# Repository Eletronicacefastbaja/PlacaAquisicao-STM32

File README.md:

# PlacaAquisicao-STM32
Repositório do Projeto da Placa de Aquisição para o micro-controlador STM32

# TODO

- Adicionar AMP-OP nas entradads analógicas
- Diminuir o tamanho da placa

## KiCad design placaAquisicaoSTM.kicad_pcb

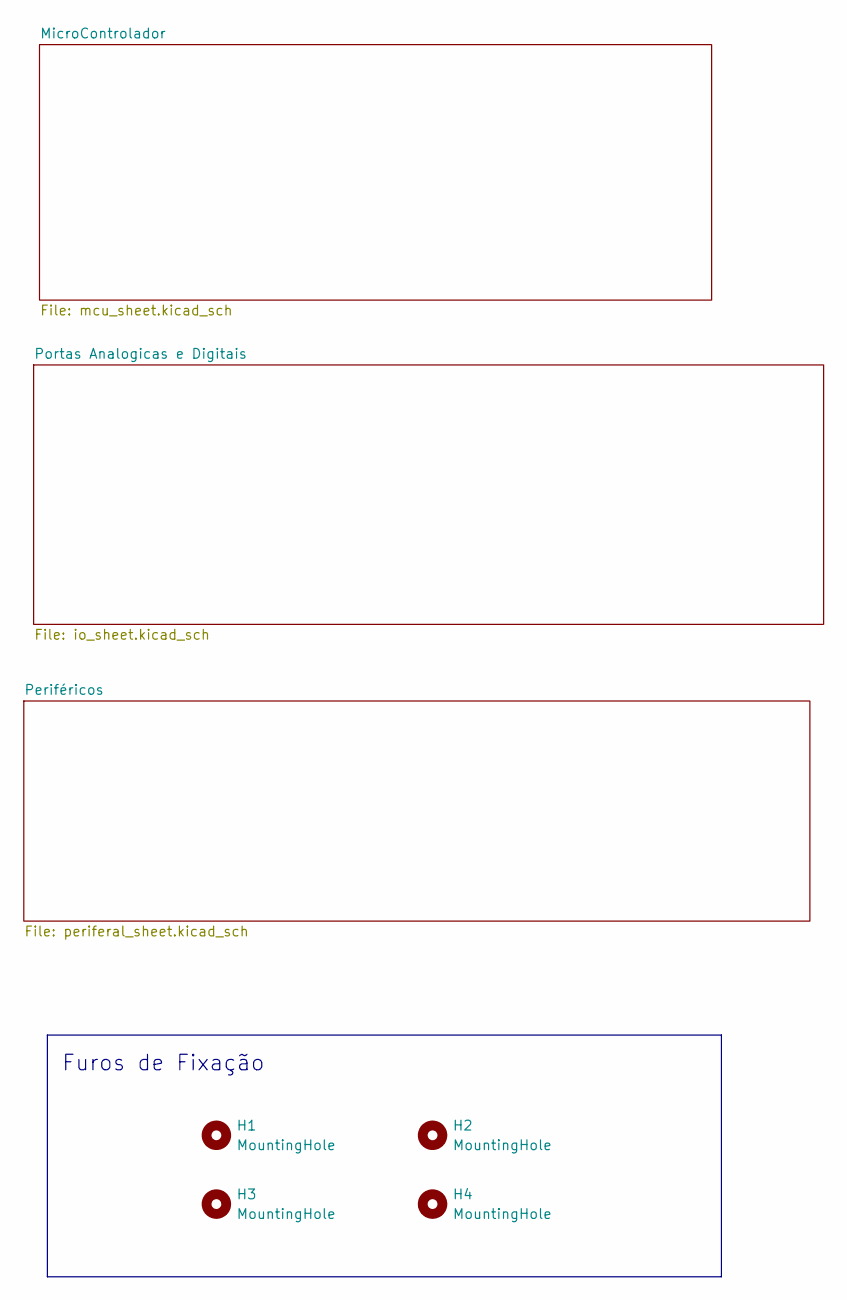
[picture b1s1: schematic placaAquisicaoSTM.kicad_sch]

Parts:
H1, H2, H3, H4: MountingHole; MountingHole_4.3mm_M4_DIN965_Pad

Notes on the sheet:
Furos de Fixação

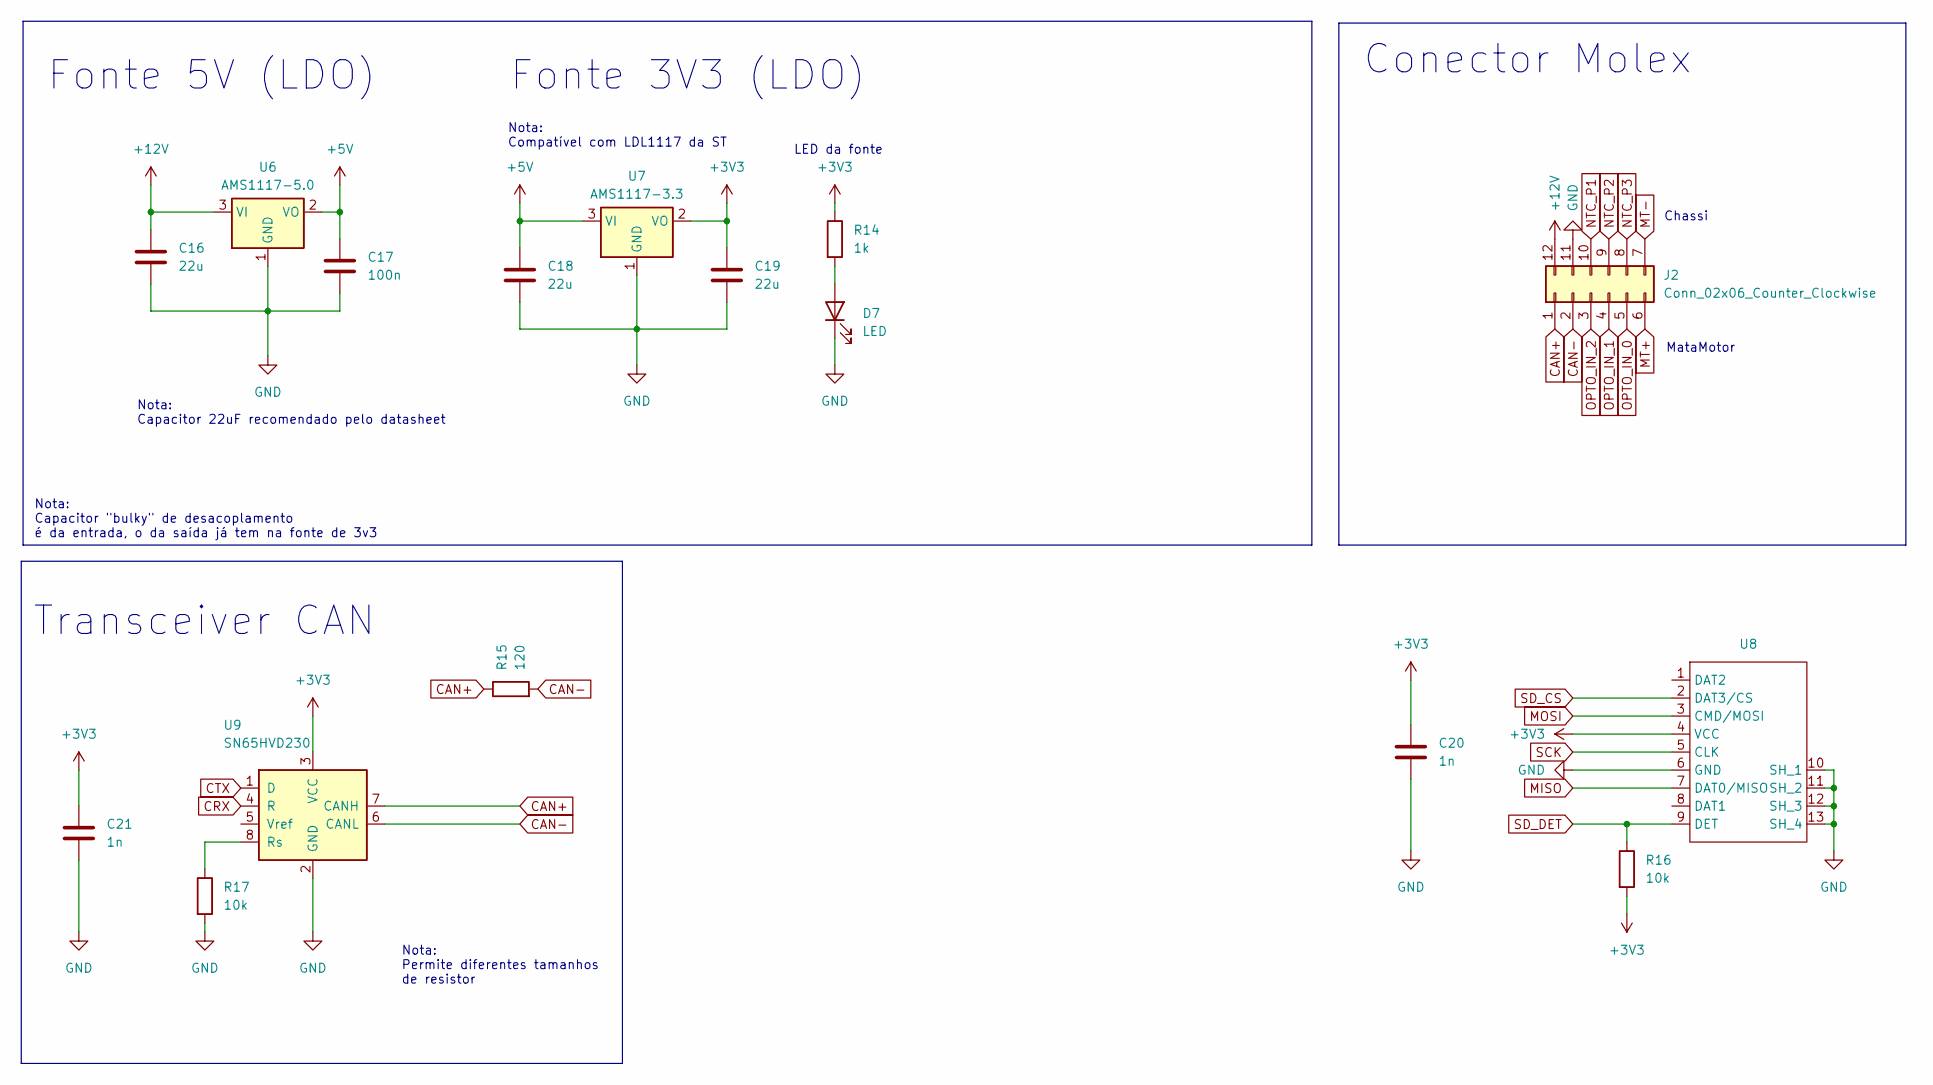
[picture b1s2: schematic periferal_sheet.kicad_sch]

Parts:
C16, C18, C19: 22u; CP_Radial_D6.3mm_P2.50mm
C17: 100n; C_0603_1608Metric_Pad1.08x0.95mm_HandSolder
C20, C21: 1n; C_0603_1608Metric_Pad1.08x0.95mm_HandSolder
D7: LED; LED_1210_HandSoldering
J2: Conn_02x06_Counter_Clockwise; DTM1512PA
R14: 1k; R_1206_3216Metric_Pad1.30x1.75mm_HandSolder
R15: 120; R_0603_1608Metric_Pad0.98x0.95mm_HandSolder
R16, R17: 10k; R_1206_3216Metric_Pad1.30x1.75mm_HandSolder
U6: AMS1117-5.0; SOT-223-3_TabPin2
U7: AMS1117-3.3; SOT-223-3_TabPin2
U8: SD-CARD-GENERIC
U9: SN65HVD230; SOIC-8_3.9x4.9mm_P1.27mm

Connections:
+3V3: C19.1, C20.1, C21.1, R14.1, R16.2, U7.2 (VO), U8.4 (VCC), U9.3 (VCC); also elsewhere on the board
+5V: C17.1, C18.1, U6.2 (VO), U7.3 (VI)
+12V: C16.1, J2.12, U6.3 (VI)
CAN+: J2.1, R15.1, U9.7 (CANH)
CAN-: J2.2, R15.2, U9.6 (CANL)
CRX: U9.4 (R); also elsewhere on the board
CTX: U9.1 (D); also elsewhere on the board
GND: C16.2, C17.2, C18.2, C19.2, C20.2, C21.2, D7.1 (K), J2.11, R17.2, U6.1 (GND), U7.1 (GND), U8.6 (GND), U8.10 (SH_1), U8.11 (SH_2), U8.12 (SH_3), U8.13 (SH_4), U9.2 (GND); also elsewhere on the board
MISO: U8.7 (DAT0/MISO); also elsewhere on the board
MOSI: U8.3 (CMD/MOSI); also elsewhere on the board
MT+: J2.6; also elsewhere on the board
MT-: J2.7; also elsewhere on the board
NTC_P1: J2.10; also elsewhere on the board
NTC_P2: J2.9; also elsewhere on the board
NTC_P3: J2.8; also elsewhere on the board
unnamed: D7.2 (A), R14.2
unnamed: R17.1, U9.8 (Rs)
OPTO_IN_0: J2.5; also elsewhere on the board
OPTO_IN_1: J2.4; also elsewhere on the board
OPTO_IN_2: J2.3; also elsewhere on the board
SCK: U8.5 (CLK); also elsewhere on the board
SD_CS: U8.2 (DAT3/CS); also elsewhere on the board
SD_DET: R16.1, U8.9 (DET); also elsewhere on the board

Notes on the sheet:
Chassi
Fonte 3V3 (LDO)
MataMotor
Fonte 5V (LDO)
Transceiver CAN
Nota: Permite diferentes tamanhos de resistor
LED da fonte
Conector Molex
Nota: Compatível com LDL1117 da ST
Nota: Capacitor 22uF recomendado pelo datasheet
Nota: Capacitor "bulky" de desacoplamento é da entrada, o da saída já tem na fonte de 3v3

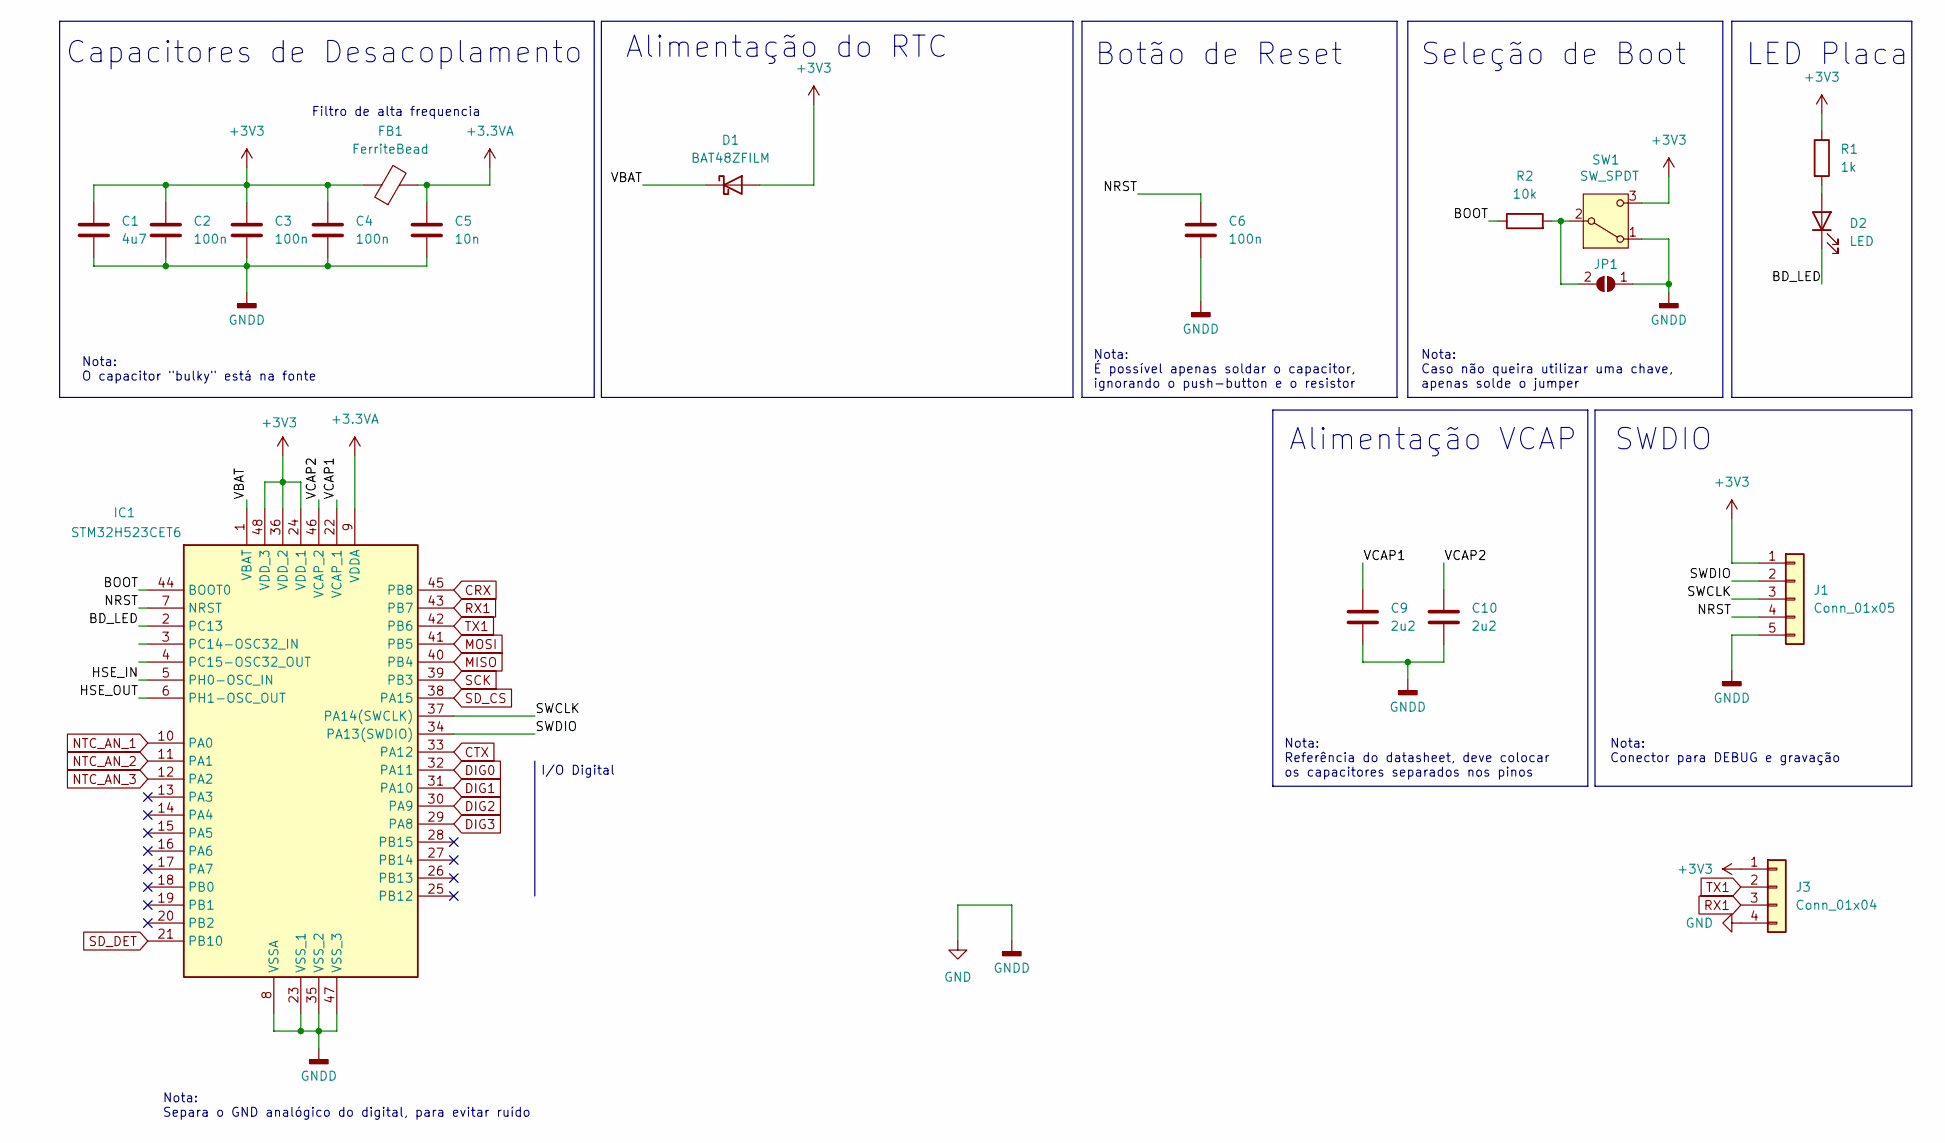
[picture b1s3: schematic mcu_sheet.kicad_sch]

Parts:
C1: 4u7; C_0805_2012Metric_Pad1.18x1.45mm_HandSolder
C2, C3, C4, C6: 100n; C_0603_1608Metric_Pad1.08x0.95mm_HandSolder
C5: 10n; C_0603_1608Metric_Pad1.08x0.95mm_HandSolder
C9, C10: 2u2; C_0603_1608Metric_Pad1.08x0.95mm_HandSolder
D1: BAT48ZFILM; D_SOD-123
D2: LED; LED_1210_HandSoldering
FB1: FerriteBead; L_0805_2012Metric_Pad1.15x1.40mm_HandSolder
IC1: STM32H523CET6; QFP50P900X900X160-48N; Mouser Part Number 511-STM32H523CET6
J1: Conn_01x05; PinHeader_1x05_P2.54mm_Vertical
J3: Conn_01x04; Molex_KK-254_AE-6410-04A_1x04_P2.54mm_Vertical
JP1: SolderJumper_2_Open; SolderJumper-2_P1.3mm_Open_RoundedPad1.0x1.5mm
R1: 1k; R_1206_3216Metric_Pad1.30x1.75mm_HandSolder
R2: 10k; R_1206_3216Metric_Pad1.30x1.75mm_HandSolder
SW1: SW_SPDT; PinHeader_1x03_P2.54mm_Vertical

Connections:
+3.3VA: C5.1, FB1.2, IC1.9 (VDDA)
+3V3: C1.1, C2.1, C3.1, C4.1, D1.2 (A), FB1.1, IC1.24 (VDD_1), IC1.36 (VDD_2), IC1.48 (VDD_3), J1.1, J3.1, R1.1, SW1.3 (C); also elsewhere on the board
/MicroControlador/BD_LED: D2.1 (K), IC1.2 (PC13)
/MicroControlador/BOOT: IC1.44 (BOOT0), R2.1
/MicroControlador/HSE_IN: IC1.5 (PH0-OSC_IN)
/MicroControlador/HSE_OUT: IC1.6 (PH1-OSC_OUT)
/MicroControlador/NRST: C6.1, IC1.7 (NRST), J1.4
/MicroControlador/SWCLK: IC1.37 (PA14(SWCLK)), J1.3
/MicroControlador/SWDIO: IC1.34 (PA13(SWDIO)), J1.2
/MicroControlador/VBAT: D1.1 (K), IC1.1 (VBAT)
/MicroControlador/VCAP1: C9.1, IC1.22 (VCAP_1)
/MicroControlador/VCAP2: C10.1, IC1.46 (VCAP_2)
CRX: IC1.45 (PB8); also elsewhere on the board
CTX: IC1.33 (PA12); also elsewhere on the board
DIG0: IC1.32 (PA11); also elsewhere on the board
DIG1: IC1.31 (PA10); also elsewhere on the board
DIG2: IC1.30 (PA9); also elsewhere on the board
DIG3: IC1.29 (PA8); also elsewhere on the board
GND: C1.2, C2.2, C3.2, C4.2, C5.2, C6.2, C9.2, C10.2, IC1.8 (VSSA), IC1.23 (VSS_1), IC1.35 (VSS_2), IC1.47 (VSS_3), J1.5, J3.4, JP1.1 (A), SW1.1 (A); also elsewhere on the board
MISO: IC1.40 (PB4); also elsewhere on the board
MOSI: IC1.41 (PB5); also elsewhere on the board
NTC_AN_1: IC1.10 (PA0); also elsewhere on the board
NTC_AN_2: IC1.11 (PA1); also elsewhere on the board
NTC_AN_3: IC1.12 (PA2); also elsewhere on the board
unnamed: D2.2 (A), R1.2
unnamed: JP1.2 (B), R2.2, SW1.2 (B)
RX1: IC1.43 (PB7), J3.3
SCK: IC1.39 (PB3); also elsewhere on the board
SD_CS: IC1.38 (PA15); also elsewhere on the board
SD_DET: IC1.21 (PB10); also elsewhere on the board
TX1: IC1.42 (PB6), J3.2

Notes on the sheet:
Alimentação do RTC
Nota: Referência do datasheet, deve colocar os capacitores separados nos pinos
Seleção de Boot
Nota: É possível apenas soldar o capacitor, ignorando o push-button e o resistor
Botão de Reset
Nota: O capacitor "bulky" está na fonte
Alimentação VCAP
Nota: Separa o GND analógico do digital, para evitar ruído
Nota: Caso não queira utilizar uma chave, apenas solde o jumper
Filtro de alta frequencia
SWDIO
Nota: Conector para DEBUG e gravação
I/O Digital
LED Placa
Capacitores de Desacoplamento

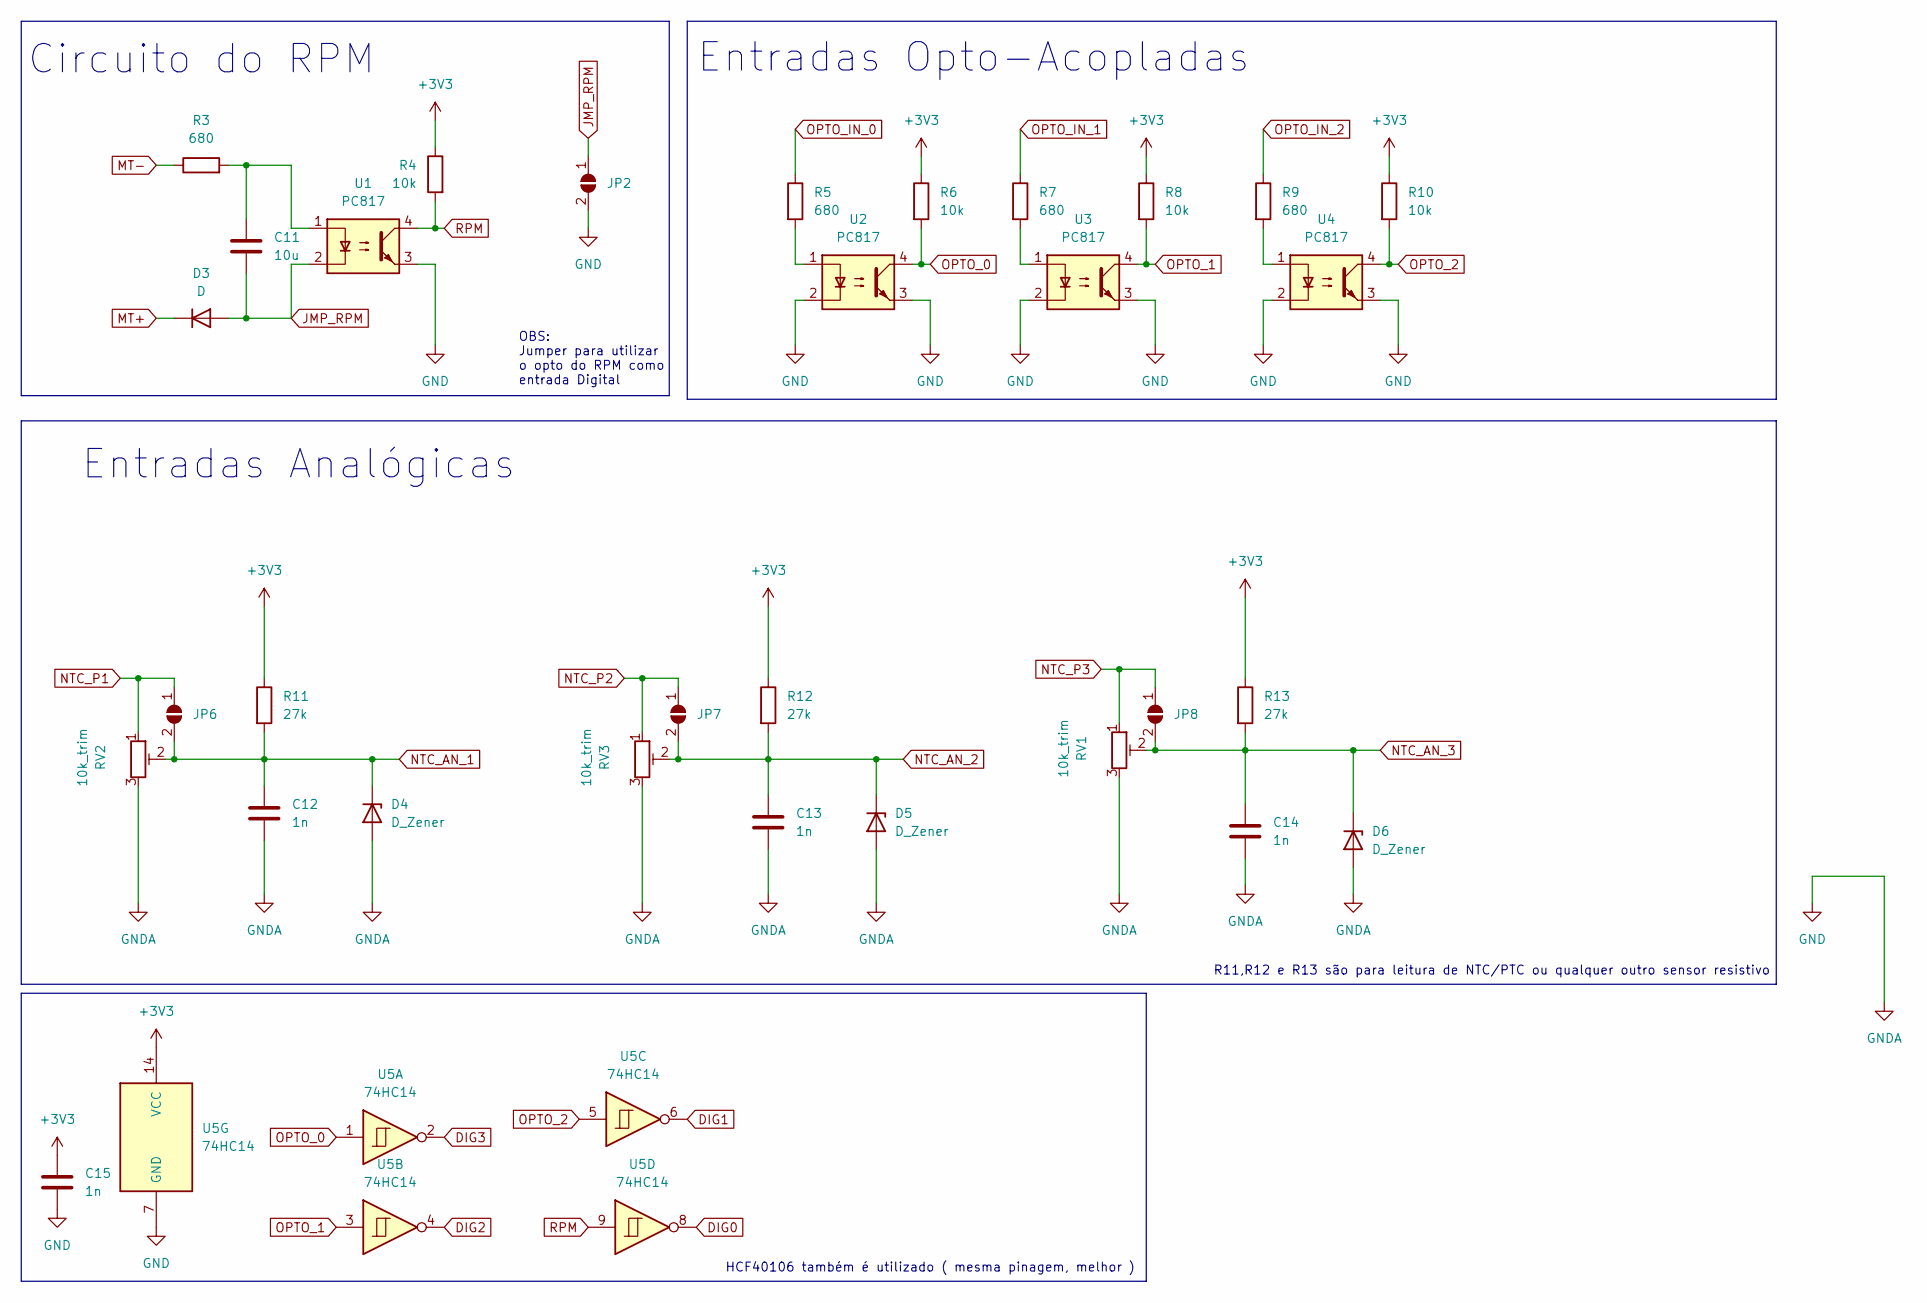
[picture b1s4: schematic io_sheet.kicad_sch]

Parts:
C11: 10u; C_0805_2012Metric_Pad1.18x1.45mm_HandSolder
C12, C13, C14, C15: 1n; C_0603_1608Metric_Pad1.08x0.95mm_HandSolder
D3: D; D_SMA_Handsoldering
D4, D5, D6: D_Zener; D_SOD-123
JP2, JP6, JP7, JP8: SolderJumper_2_Open; SolderJumper-2_P1.3mm_Open_RoundedPad1.0x1.5mm
R3, R5, R7, R9: 680; R_1206_3216Metric_Pad1.30x1.75mm_HandSolder
R4, R6, R8, R10: 10k; R_1206_3216Metric_Pad1.30x1.75mm_HandSolder
R11, R12, R13: 27k; R_1206_3216Metric_Pad1.30x1.75mm_HandSolder
RV1, RV2, RV3: 10k_trim; Potentiometer_Bourns_3296W_Vertical
U1, U2, U3, U4: PC817; SO-4_HandSoldering
U5: 74HC14

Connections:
+3V3: C15.1, R4.1, R6.1, R8.1, R10.1, R11.1, R12.1, R13.1, U5.14 (VCC); also elsewhere on the board
DIG0: U5.8; also elsewhere on the board
DIG1: U5.6; also elsewhere on the board
DIG2: U5.4; also elsewhere on the board
DIG3: U5.2; also elsewhere on the board
GND: C12.2, C13.2, C14.2, C15.2, D4.2 (A), D5.2 (A), D6.2 (A), JP2.2 (B), RV1.3, RV2.3, RV3.3, U1.3, U2.2, U2.3, U3.2, U3.3, U4.2, U4.3, U5.7 (GND); also elsewhere on the board
JMP_RPM: C11.2, D3.2 (A), JP2.1 (A), U1.2
MT+: D3.1 (K); also elsewhere on the board
MT-: R3.1; also elsewhere on the board
NTC_AN_1: C12.1, D4.1 (K), JP6.2 (B), R11.2, RV2.2; also elsewhere on the board
NTC_AN_2: C13.1, D5.1 (K), JP7.2 (B), R12.2, RV3.2; also elsewhere on the board
NTC_AN_3: C14.1, D6.1 (K), JP8.2 (B), R13.2, RV1.2; also elsewhere on the board
NTC_P1: JP6.1 (A), RV2.1; also elsewhere on the board
NTC_P2: JP7.1 (A), RV3.1; also elsewhere on the board
NTC_P3: JP8.1 (A), RV1.1; also elsewhere on the board
unnamed: C11.1, R3.2, U1.1
unnamed: R5.2, U2.1
unnamed: R7.2, U3.1
unnamed: R9.2, U4.1
OPTO_0: R6.2, U2.4, U5.1
OPTO_1: R8.2, U3.4, U5.3
OPTO_2: R10.2, U4.4, U5.5
OPTO_IN_0: R5.1; also elsewhere on the board
OPTO_IN_1: R7.1; also elsewhere on the board
OPTO_IN_2: R9.1; also elsewhere on the board
RPM: R4.2, U1.4, U5.9

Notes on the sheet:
OBS: Jumper para utilizar o opto do RPM como entrada Digital
R11,R12 e R13 são para leitura de NTC/PTC ou qualquer outro sensor resistivo
Circuito do RPM
Entradas Opto-Acopladas
Entradas Analógicas
HCF40106 também é utilizado ( mesma pinagem, melhor )

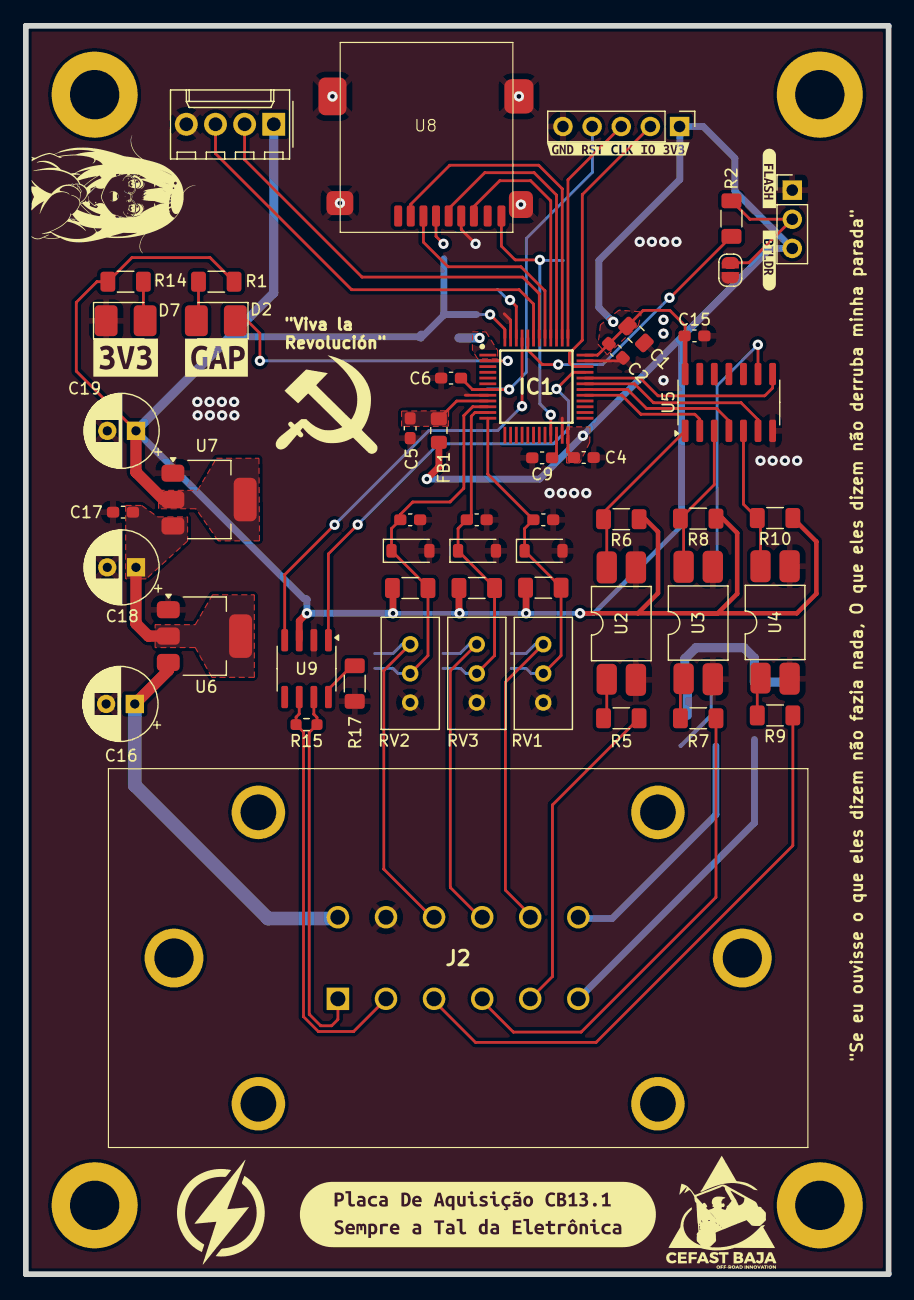
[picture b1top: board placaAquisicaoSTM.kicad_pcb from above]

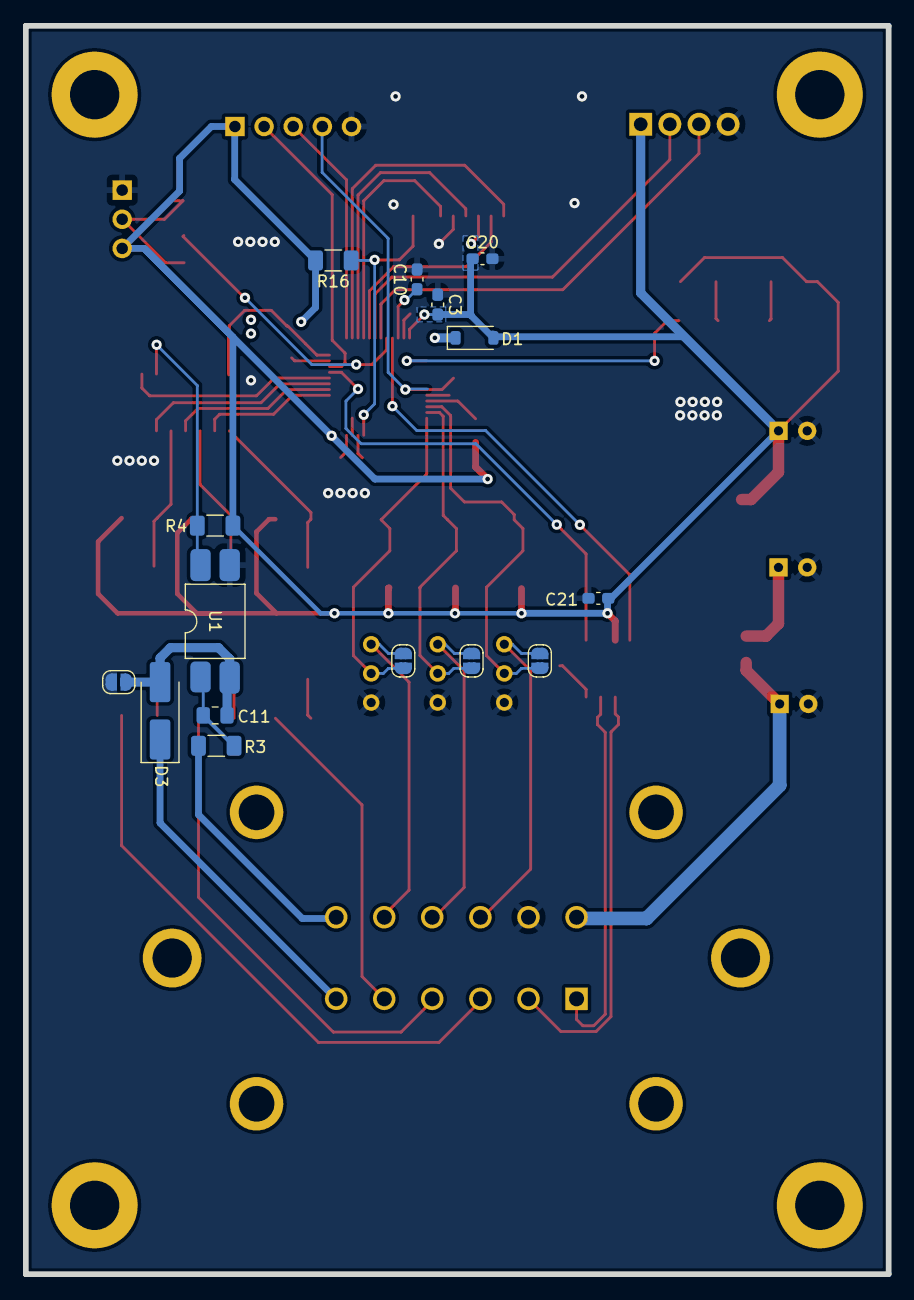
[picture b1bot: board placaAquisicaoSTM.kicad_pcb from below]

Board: 2 copper layers, 75.2 x 108.8 mm, 76 parts (16 on the bottom side), 52 nets.

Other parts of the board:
kibuzzard-67EDAA6F: G***; kibuzzard-67EDAA6F
kibuzzard-683E47A0: G***; kibuzzard-683E47A0
kibuzzard-6758F24A: G***; kibuzzard-6758F24A
kibuzzard-6758FD86: G***; kibuzzard-6758FD86
kibuzzard-67572A93: G***; kibuzzard-67572A93
kibuzzard-67572AD3: G***; kibuzzard-67572AD3

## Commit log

2024-11-23 Adicionei o gitignore para a pasta de backups
2024-11-23 Adicionei os arquivos da placa de aquisicao e mudei o gitignore para ignorar lck e auto saved
2024-11-23 Comecei a adicionar a parte das entradas e continuo mexendo na parte do STM32
2024-11-26 Troquei o micro para STM32H523, adicionei o cristal HSE, circuito da fonte de 5V e 3v3, CAN, SD
2024-11-30 Alterei o nome para o par diferencial do CAN, adicionei capacitores de desacoplamento para todas as alimentacoes
2024-12-18 Removi as entradas analógicas, projeto delas estava errado
2025-01-27 Alterei para ter 3 portas analogicas, adaptei o circuito do RPM para ter um jumper que permite usar como entrada digital
2025-04-15 Diminui o tamanho da placa
2025-04-16 Removi o botao de reset do design
2025-06-03 Troquei o conector para o conector DEUTSCH
